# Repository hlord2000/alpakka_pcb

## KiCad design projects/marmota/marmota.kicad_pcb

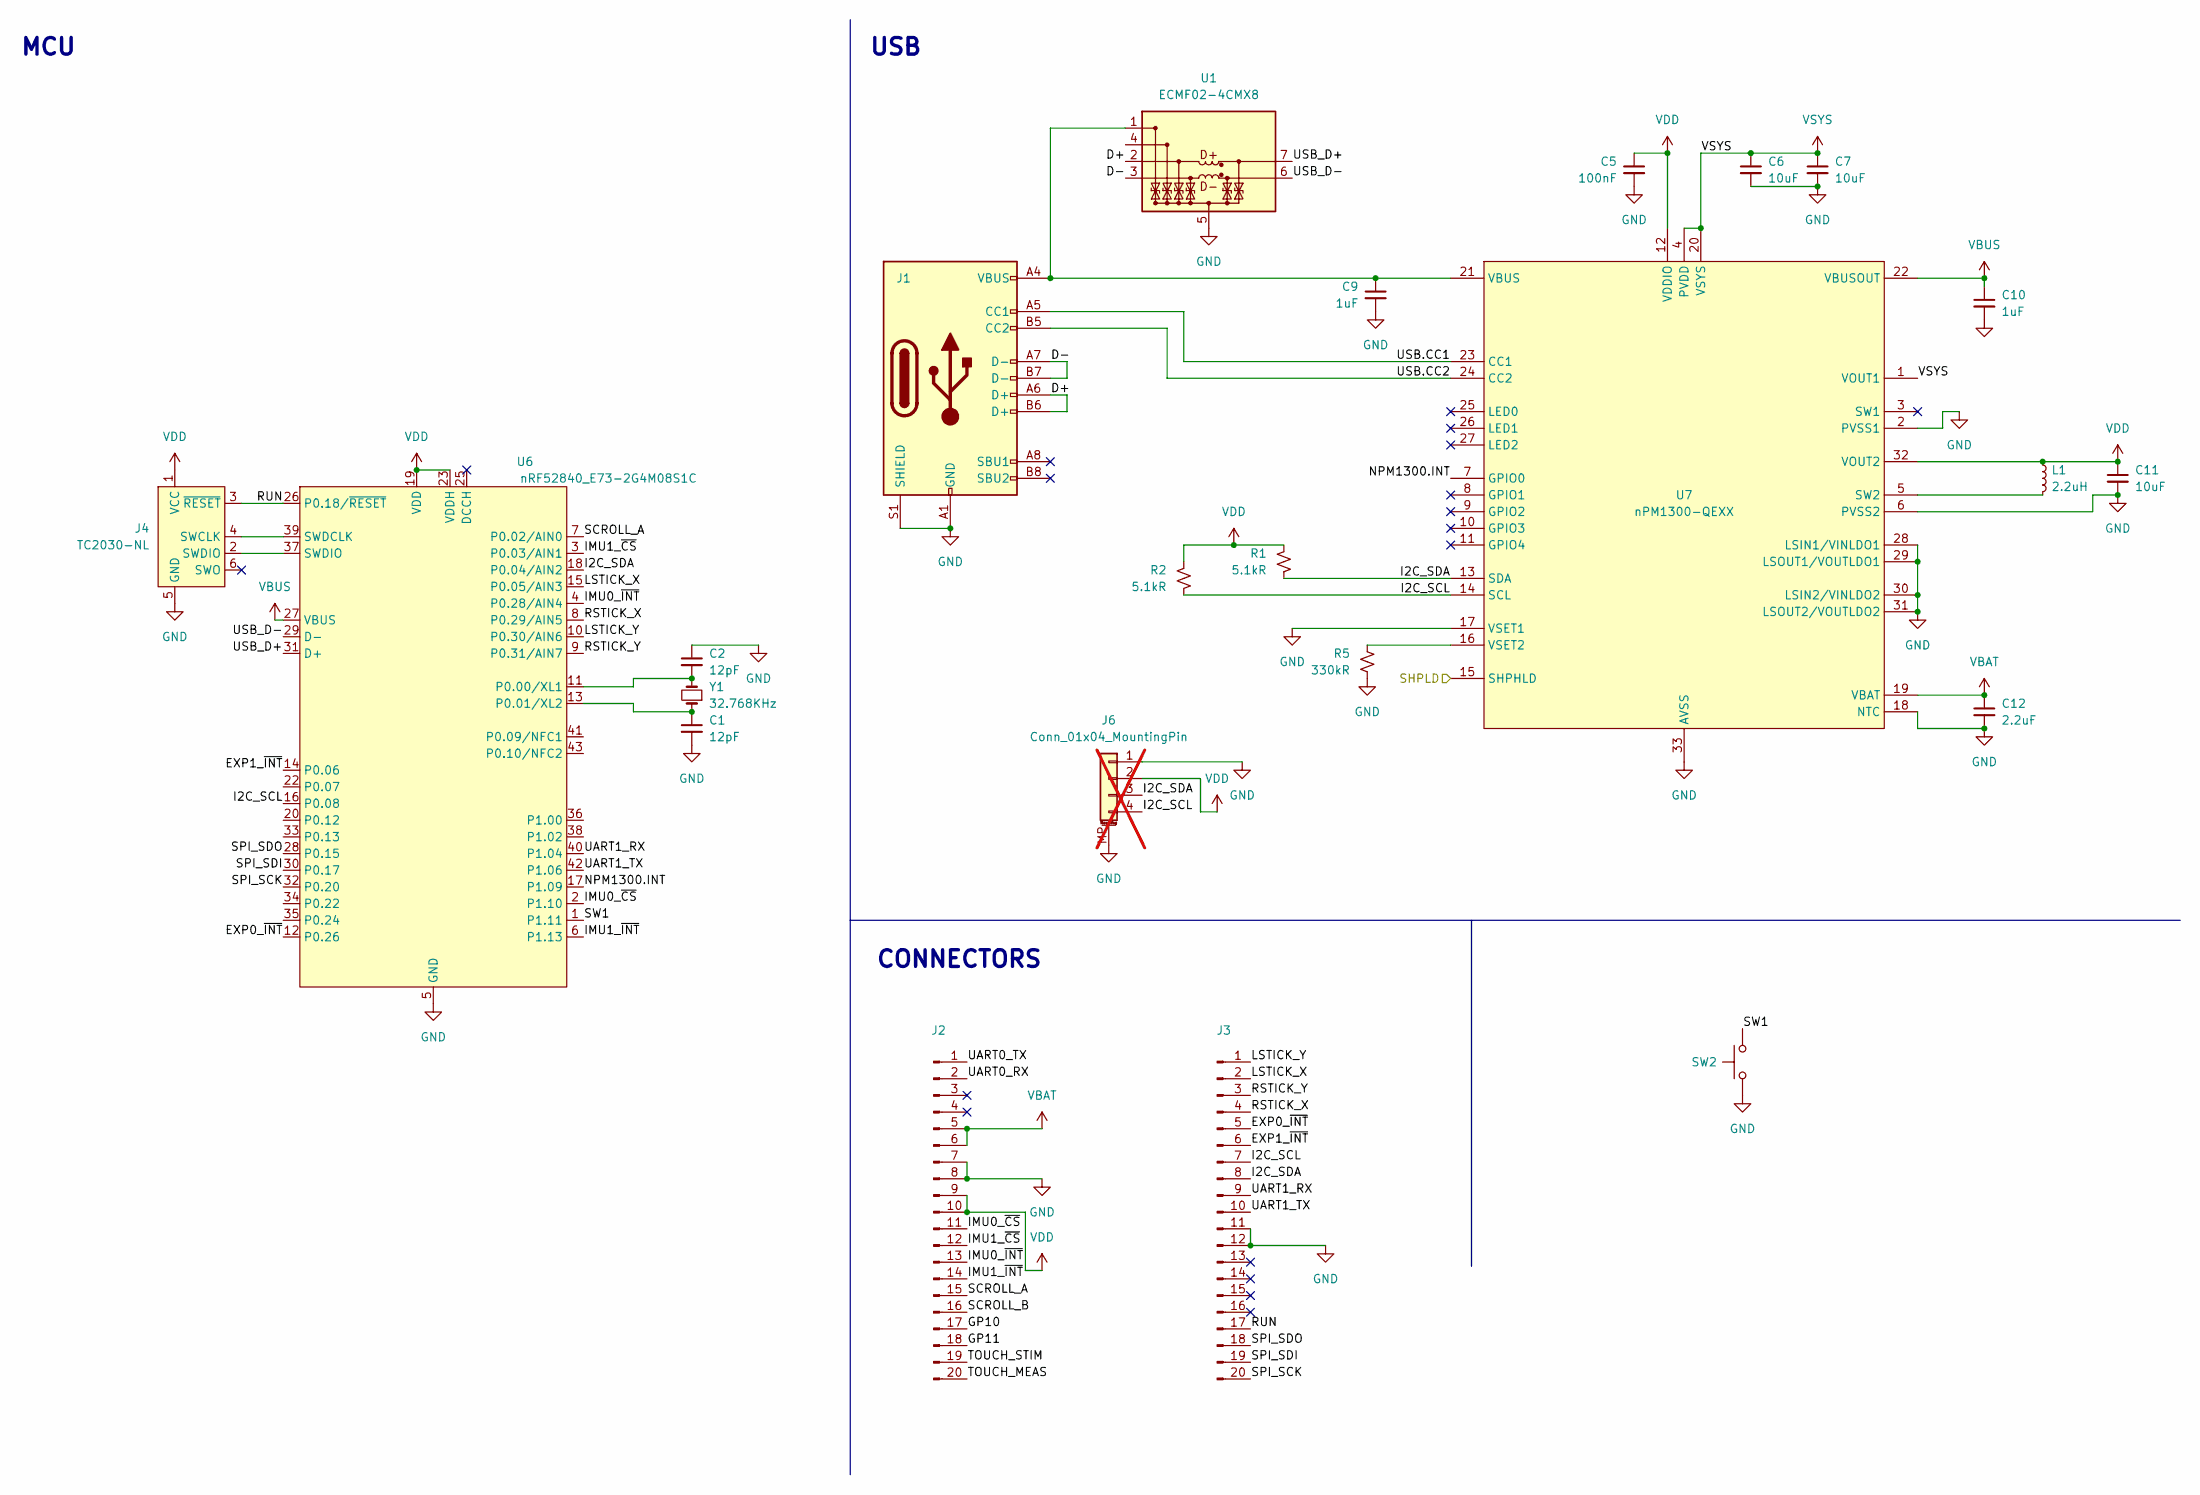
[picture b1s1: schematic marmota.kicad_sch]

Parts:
C1, C2: 12pF; C_0402_1005Metric
C5: 100nF; C_0402_1005Metric; LCSC C307331
C6, C7, C11: 10uF; C_0603_1608Metric; LCSC C96446
C9, C10: 1uF; C_0603_1608Metric; LCSC C15849
C12: 2.2uF; C_0603_1608Metric; LCSC C23630
J1: USB_C; USB_C3019717; LCSC C3019717
J2, J3: Conn_01x20_Pin; Hirose_DF12NB; LCSC C2917815
J4: TC2030-NL; Tag-Connect_TC2030-IDC-NL_2x03_P1.27mm_Vertical
J6: Conn_01x04_MountingPin; JST_SH_SM04B-SRSS-TB_1x04-1MP_P1.00mm_Horizontal; not fitted
L1: 2.2uH; L_0603_1608Metric; LCSC C337910
R1, R2: 5.1kR; R_0402_1005Metric
R5: 330kR; R_0402_1005Metric; LCSC C25778
SW2: Button side; Alpsalpine_SKSC; LCSC C115362
U1: ECMF02-4CMX8; ST_UQFN-8L_1.2x2.5mm_P0.5mm
U6: nRF52840_E73-2G4M08S1C; LCSC C356849
U7: nPM1300-QEXX; QFN-32-1EP_5x5mm_P0.5mm_EP3.6x3.6mm_ThermalVias; LCSC C7466043
Y1: 32.768KHz; Crystal_SMD_2012-2Pin_2.0x1.2mm

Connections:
/D+: J1.A6 (D+), J1.B6 (D+), U1.2 (D-_in)
/D-: J1.A7 (D-), J1.B7 (D-), U1.3 (D+_in)
/EXP0_~INT: J3.5, U6.12 (P0.26)
/EXP1_~INT: J3.6, U6.14 (P0.06)
/GP10: J2.17
/GP11: J2.18
/I2C_SCL: J3.7, J6.4, R2.2, U6.16 (P0.08), U7.14 (SCL)
/I2C_SDA: J3.8, J6.3, R1.2, U6.18 (P0.04/AIN2), U7.13 (SDA)
/IMU0_~CS: J2.11, U6.2 (P1.10)
/IMU0_~INT: J2.13, U6.4 (P0.28/AIN4)
/IMU1_~CS: J2.12, U6.3 (P0.03/AIN1)
/IMU1_~INT: J2.14, U6.6 (P1.13)
/LSTICK_X: J3.2, U6.15 (P0.05/AIN3)
/LSTICK_Y: J3.1, U6.10 (P0.30/AIN6)
/NPM1300.INT: U6.17 (P1.09), U7.7 (GPIO0)
/RSTICK_X: J3.4, U6.8 (P0.29/AIN5)
/RSTICK_Y: J3.3, U6.9 (P0.31/AIN7)
/RUN: J3.17, J4.3 (~RESET), U6.26 (P0.18/~RESET)
/SCROLL_A: J2.15, U6.7 (P0.02/AIN0)
/SCROLL_B: J2.16
/SHPLD: U7.15 (SHPHLD)
/SPI_SCK: J3.20, U6.32 (P0.20)
/SPI_SDI: J3.19, U6.30 (P0.17)
/SPI_SDO: J3.18, U6.28 (P0.15)
/SW1: SW2.2, U6.1 (P1.11)
/TOUCH_MEAS: J2.20
/TOUCH_STIM: J2.19
/UART0_RX: J2.2
/UART0_TX: J2.1
/UART1_RX: J3.9, U6.40 (P1.04)
/UART1_TX: J3.10, U6.42 (P1.06)
/USB.CC1: J1.A5 (CC1), U7.23 (CC1)
/USB.CC2: J1.B5 (CC2), U7.24 (CC2)
/USB_D+: U1.7 (D-_out), U6.31 (D+)
/USB_D-: U1.6 (D+_out), U6.29 (D-)
GND: C1.2, C2.1, C5.2, C6.2, C7.2, C9.2, C10.2, C11.2, C12.2, J1.A1 (GND), J1.A12 (GND), J1.B1 (GND), J1.B12 (GND), J1.S1 (SHIELD), J2.7, J2.8, J3.11, J3.12, J4.5 (GND), J6.1, J6.MP (MountPin), R5.2, SW2.1, U1.5 (GND), U1.8 (GND), U6.5 (GND), U6.21 (GND), U6.24 (GND), U7.2 (PVSS1), U7.6 (PVSS2), U7.17 (VSET1), U7.18 (NTC), U7.28 (LSIN1/VINLDO1), U7.29 (LSOUT1/VOUTLDO1), U7.30 (LSIN2/VINLDO2), U7.31 (LSOUT2/VOUTLDO2), U7.33 (AVSS)
unnamed: J4.4 (SWCLK), U6.39 (SWDCLK)
unnamed: J4.2 (SWDIO), U6.37 (SWDIO)
unnamed: C9.1, J1.A4 (VBUS), J1.A9 (VBUS), J1.B4 (VBUS), J1.B9 (VBUS), U1.1 (VBUS), U7.21 (VBUS)
unnamed: C2.2, U6.11 (P0.00/XL1), Y1.2
unnamed: C1.1, U6.13 (P0.01/XL2), Y1.1
unnamed: L1.2, U7.5 (SW2)
unnamed: R5.1, U7.16 (VSET2)
VBAT: C12.1, J2.5, J2.6, U7.19 (VBAT)
VBUS: C10.1, U6.27 (VBUS), U7.22 (VBUSOUT)
VDD: C5.1, C11.1, J2.9, J2.10, J4.1 (VCC), J6.2, L1.1, R1.1, R2.1, U6.19 (VDD), U6.23 (VDDH), U7.12 (VDDIO), U7.32 (VOUT2)
VSYS: C6.1, C7.1, U7.1 (VOUT1), U7.4 (PVDD), U7.20 (VSYS)

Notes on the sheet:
CONNECTORS
USB
MCU

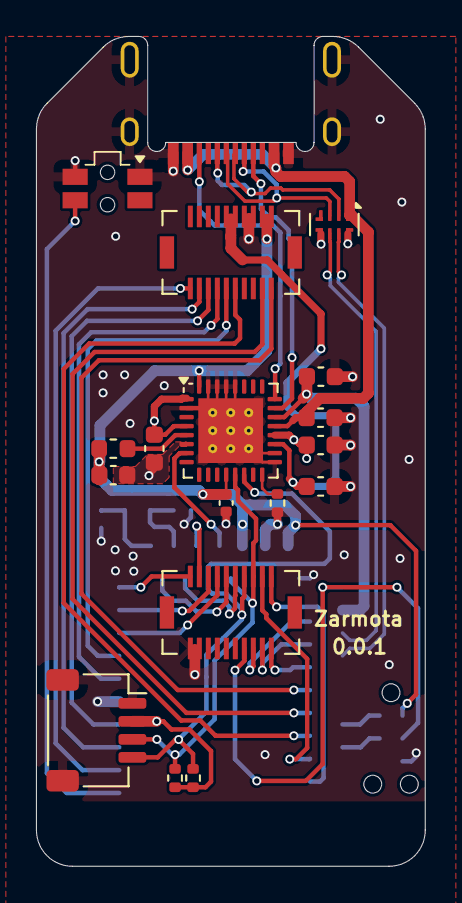
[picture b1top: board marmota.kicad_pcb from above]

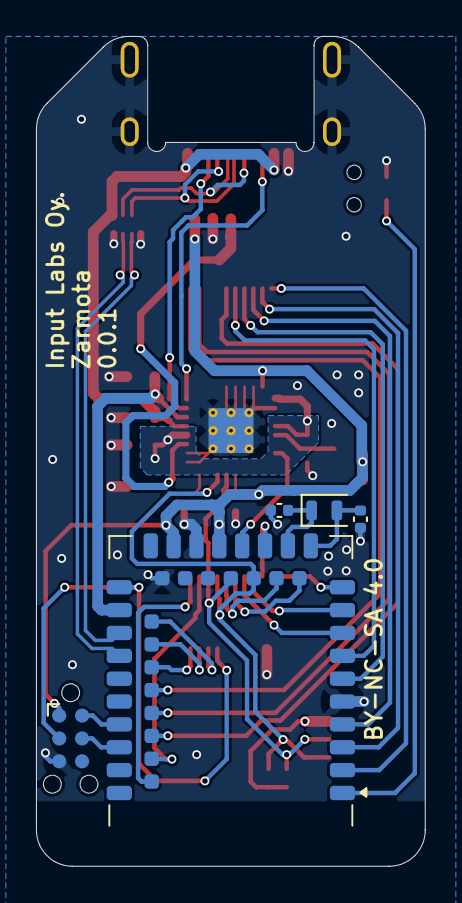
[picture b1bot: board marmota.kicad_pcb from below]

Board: 4 copper layers, 21.6 x 46.1 mm, 23 parts (5 on the bottom side), 39 nets.

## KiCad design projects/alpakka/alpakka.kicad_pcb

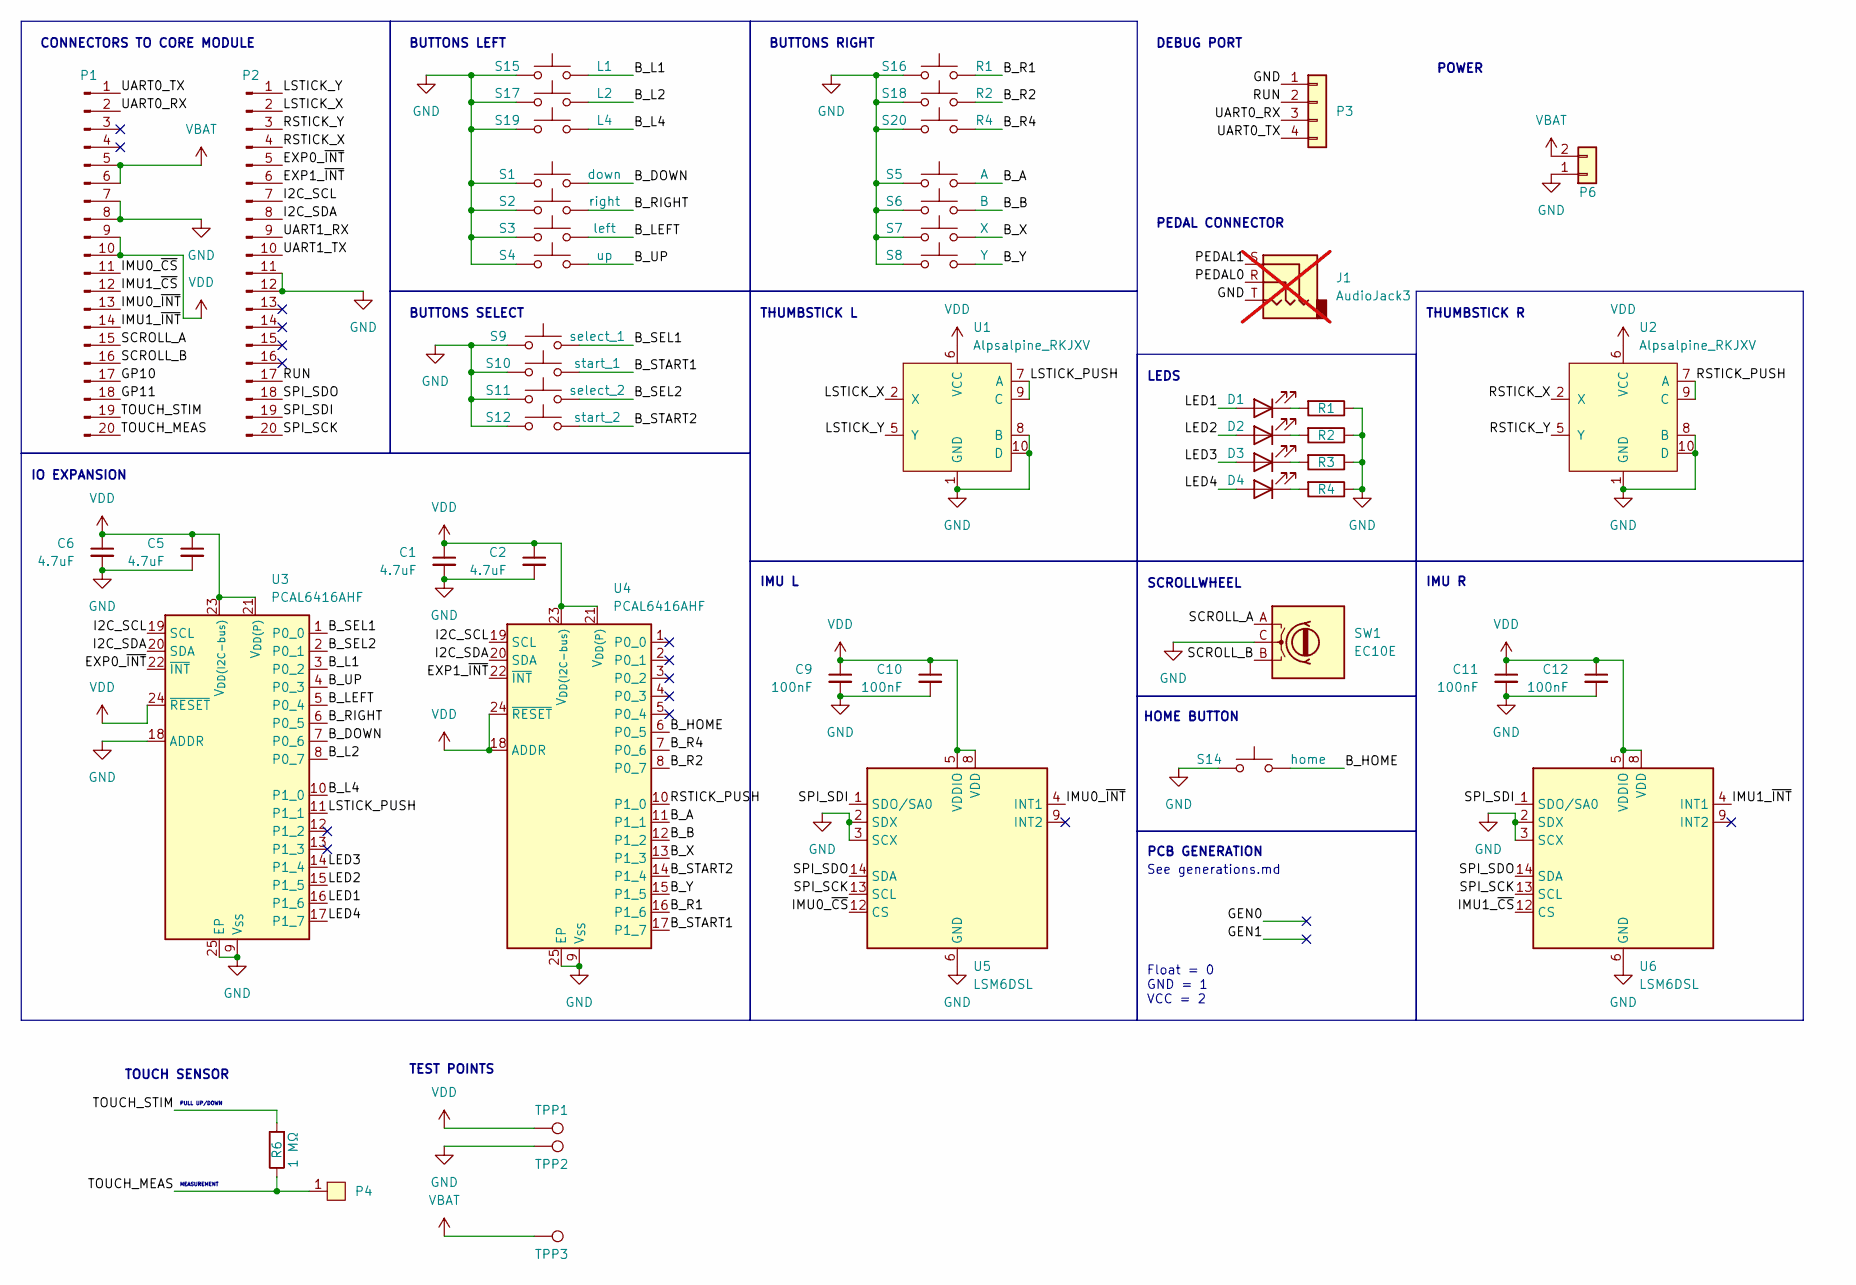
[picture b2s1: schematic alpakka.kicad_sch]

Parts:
C1, C2, C5, C6: 4.7uF; C_0603_1608Metric
C9, C10, C11, C12: 100nF; C_0402_1005Metric
D1, D2, D3, D4: Diode; D_0603_1608Metric; LCSC C2290
J1: AudioJack3; Jack_3.5mm_CUI_SJ-3523-SMT_Horizontal; not fitted
P1, P2: Conn_01x20_Pin; Hirose_DF12NB_receptacle; LCSC C2917814
P3: Conn_01x04; XKB_X6511FRS-04; LCSC C5142237
P4: Blade; HRO_BC-25-3P; LCSC C707322
P6: Conn_01x02; JST_PH_S2B-PH-K_1x02_P2.00mm_Horizontal; LCSC C5359610
R1, R2, R3, R4: 20 Ω; R_0603_1608Metric; LCSC C22950
R6: 1 MΩ; R_0402_1005Metric; LCSC C26083
S1: down; Alpsalpine_SKPM; LCSC C115348
S2: right; Alpsalpine_SKPM; LCSC C115348
S3: left; Alpsalpine_SKPM; LCSC C115348
S4: up; Alpsalpine_SKPM; LCSC C115348
S5: A; Alpsalpine_SKPM; LCSC C115348
S6: B; Alpsalpine_SKPM; LCSC C115348
S7: X; Alpsalpine_SKPM; LCSC C115348
S8: Y; Alpsalpine_SKPM; LCSC C115348
S9: select_1; Alpsalpine_SKPM; LCSC C115348
S10: start_1; Alpsalpine_SKPM; LCSC C115348
S11: select_2; Alpsalpine_SKPM; LCSC C115348
S12: start_2; Alpsalpine_SKPM; LCSC C115348
S14: home; Alpsalpine_SKPM; LCSC C115348
S15: L1; Alpsalpine_SKHHL; LCSC C125031
S16: R1; Alpsalpine_SKHHL; LCSC C125031
S17: L2; Alpsalpine_SKQG; LCSC C202424
S18: R2; Alpsalpine_SKQG; LCSC C202424
S19: L4; Alpsalpine_SKQG; LCSC C202424
S20: R4; Alpsalpine_SKQG; LCSC C202424
SW1: EC10E; Alpsalpine_EC10E
TPP1, TPP2, TPP3: Endpoint; TestPoint_Pad_D1.0mm
U1, U2: Alpsalpine_RKJXV; Alpsalpine_RKJXV122400R
U3, U4: PCAL6416AHF; HVQFN-24-1EP_4x4mm_P0.5mm_EP2.1x2.1mm
U5, U6: LSM6DSL; LGA-14_3x2.5mm_P0.5mm_LayoutBorder3x4y

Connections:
/B_A: S5.2, U4.11 (P1_1)
/B_B: S6.2, U4.12 (P1_2)
/B_DOWN: S1.2, U3.7 (P0_6)
/B_HOME: S14.2, U4.6 (P0_5)
/B_L1: S15.2, U3.3 (P0_2)
/B_L2: S17.2, U3.8 (P0_7)
/B_L4: S19.2, U3.10 (P1_0)
/B_LEFT: S3.2, U3.5 (P0_4)
/B_R1: S16.2, U4.16 (P1_6)
/B_R2: S18.2, U4.8 (P0_7)
/B_R4: S20.2, U4.7 (P0_6)
/B_RIGHT: S2.2, U3.6 (P0_5)
/B_SEL1: S9.2, U3.1 (P0_0)
/B_SEL2: S11.2, U3.2 (P0_1)
/B_START1: S10.2, U4.17 (P1_7)
/B_START2: S12.2, U4.14 (P1_4)
/B_UP: S4.2, U3.4 (P0_3)
/B_X: S7.2, U4.13 (P1_3)
/B_Y: S8.2, U4.15 (P1_5)
/EXP0_~INT: P2.5, U3.22 (~INT)
/EXP1_~INT: P2.6, U4.22 (~INT)
/GP10: P1.17
/GP11: P1.18
/I2C_SCL: P2.7, U3.19 (SCL), U4.19 (SCL)
/I2C_SDA: P2.8, U3.20 (SDA), U4.20 (SDA)
/IMU0_~CS: P1.11, U5.12 (CS)
/IMU0_~INT: P1.13, U5.4 (INT1)
/IMU1_~CS: P1.12, U6.12 (CS)
/IMU1_~INT: P1.14, U6.4 (INT1)
/LED1: D1.2 (A), U3.16 (P1_6)
/LED2: D2.2 (A), U3.15 (P1_5)
/LED3: D3.2 (A), U3.14 (P1_4)
/LED4: D4.2 (A), U3.17 (P1_7)
/LSTICK_PUSH: U1.7 (A), U1.9 (C), U3.11 (P1_1)
/LSTICK_X: P2.2, U1.2 (X)
/LSTICK_Y: P2.1, U1.5 (Y)
/RSTICK_PUSH: U2.7 (A), U2.9 (C), U4.10 (P1_0)
/RSTICK_X: P2.4, U2.2 (X)
/RSTICK_Y: P2.3, U2.5 (Y)
/RUN: P2.17, P3.2
/SCROLL_A: P1.15, SW1.A
/SCROLL_B: P1.16, SW1.B
/SPI_SCK: P2.20, U5.13 (SCL), U6.13 (SCL)
/SPI_SDI: P2.19, U5.1 (SDO/SA0), U6.1 (SDO/SA0)
/SPI_SDO: P2.18, U5.14 (SDA), U6.14 (SDA)
/TOUCH_MEAS: P1.20, P4.1, R6.1
/TOUCH_STIM: P1.19, R6.2
/UART0_RX: P1.2, P3.3
/UART0_TX: P1.1, P3.4
/UART1_RX: P2.9
/UART1_TX: P2.10
GND: C1.2, C2.2, C5.2, C6.2, C9.2, C10.2, C11.2, C12.2, J1.T, P1.7, P1.8, P2.11, P2.12, P3.1, P6.1, R1.1, R2.1, R3.1, R4.1, S1.1, S2.1, S3.1, S4.1, S5.1, S6.1, S7.1, S8.1, S9.1, S10.1, S11.1, S12.1, S14.1, S15.1, S16.1, S17.1, S18.1, S19.1, S20.1, SW1.C, TPP2.1, U1.1 (GND), U1.4 (GND), U1.8 (B), U1.10 (D), U2.1 (GND), U2.4 (GND), U2.8 (B), U2.10 (D), U3.9 (V_{SS}), U3.18 (ADDR), U3.25 (EP), U4.9 (V_{SS}), U4.25 (EP), U5.2 (SDX), U5.3 (SCX), U5.6 (GND), U5.7 (GND), U6.2 (SDX), U6.3 (SCX), U6.6 (GND), U6.7 (GND)
unnamed: D1.1 (K), R1.2
unnamed: D2.1 (K), R2.2
unnamed: D3.1 (K), R3.2
unnamed: D4.1 (K), R4.2
VBAT: P1.5, P1.6, P6.2, TPP3.1
VDD: C1.1, C2.1, C5.1, C6.1, C9.1, C10.1, C11.1, C12.1, P1.9, P1.10, TPP1.1, U1.3 (VCC), U1.6 (VCC), U2.3 (VCC), U2.6 (VCC), U3.21 (V_{DD(P)}), U3.23 (V_{DD(I2C-bus)}), U3.24 (~RESET), U4.18 (ADDR), U4.21 (V_{DD(P)}), U4.23 (V_{DD(I2C-bus)}), U4.24 (~RESET), U5.5 (VDDIO), U5.8 (VDD), U6.5 (VDDIO), U6.8 (VDD)

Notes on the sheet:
SCROLLWHEEL
DEBUG PORT
THUMBSTICK R
THUMBSTICK L
IMU L
PCB GENERATION
HOME BUTTON
BUTTONS SELECT
Float = 0 GND = 1 VCC = 2
TEST POINTS
CONNECTORS TO CORE MODULE
PEDAL CONNECTOR
TOUCH SENSOR
IO EXPANSION
LEDS
BUTTONS LEFT
MEASUREMENT
BUTTONS RIGHT
IMU R
POWER
See generations.md
PULL UP/DOWN

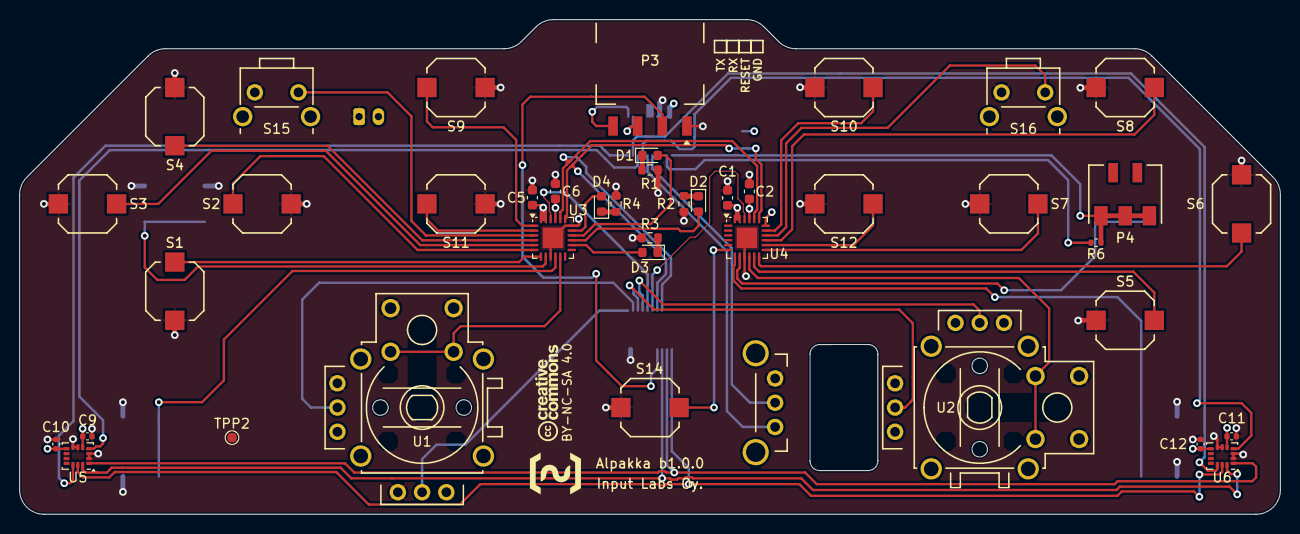
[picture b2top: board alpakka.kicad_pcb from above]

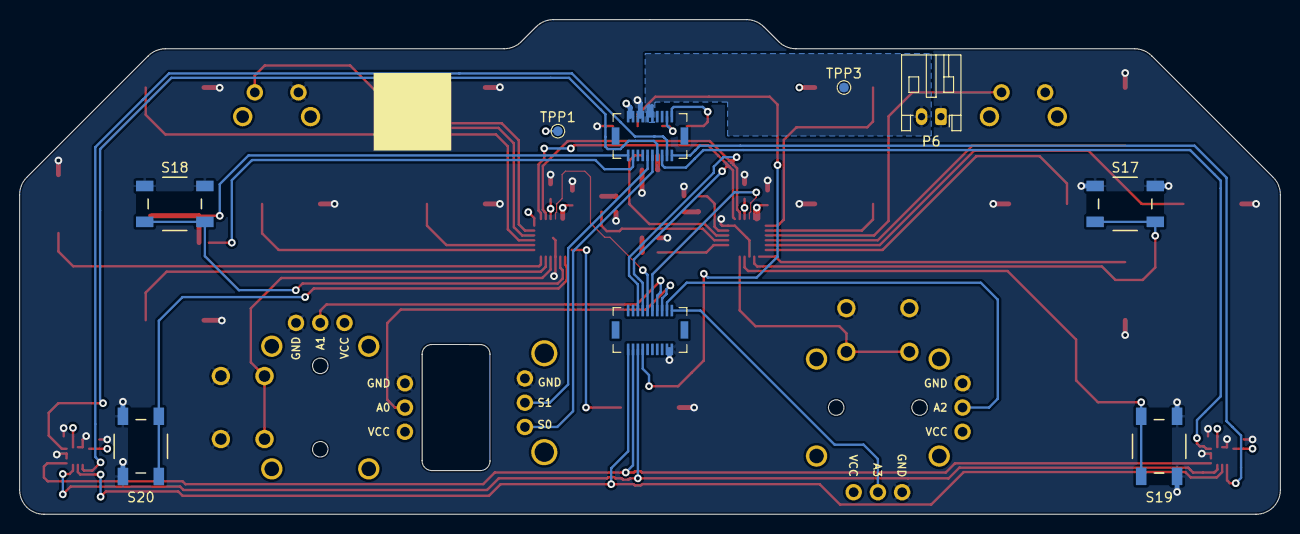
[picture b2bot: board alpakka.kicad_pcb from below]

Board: 4 copper layers, 130.0 x 51.0 mm, 51 parts (9 on the bottom side), 54 nets.

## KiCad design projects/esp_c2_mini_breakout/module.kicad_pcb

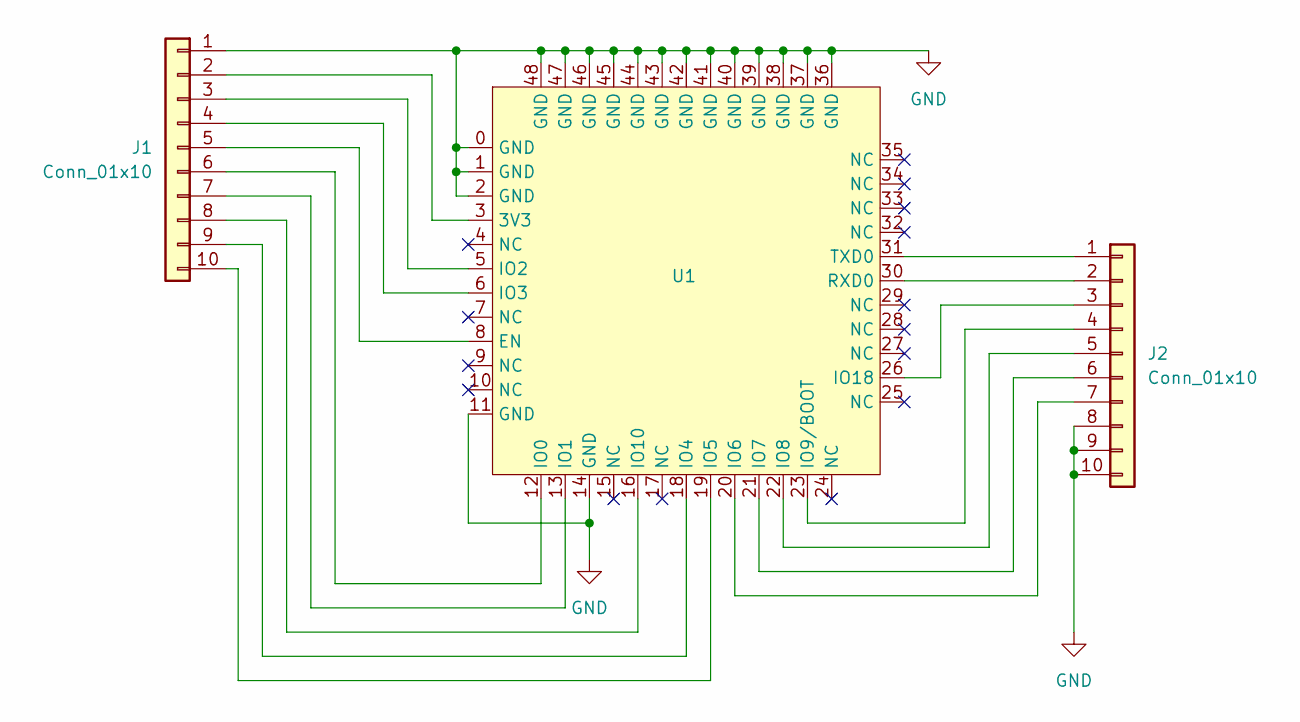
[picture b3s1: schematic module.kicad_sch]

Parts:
J1, J2: Conn_01x10; PinHeader_1x10_P2.54mm_Vertical
U1: Espressif_ESP32_mini; LCSC C3013915

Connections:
GND: J1.1, J2.8, J2.9, J2.10, U1.0 (GND), U1.1 (GND), U1.2 (GND), U1.11 (GND), U1.14 (GND), U1.36 (GND), U1.37 (GND), U1.38 (GND), U1.39 (GND), U1.40 (GND), U1.41 (GND), U1.42 (GND), U1.43 (GND), U1.44 (GND), U1.45 (GND), U1.46 (GND), U1.47 (GND), U1.48 (GND)
unnamed: J1.2, U1.3 (3V3)
unnamed: J1.3, U1.5 (IO2)
unnamed: J1.4, U1.6 (IO3)
unnamed: J1.5, U1.8 (EN)
unnamed: J1.6, U1.12 (IO0)
unnamed: J1.7, U1.13 (IO1)
unnamed: J1.8, U1.16 (IO10)
unnamed: J1.9, U1.18 (IO4)
unnamed: J1.10, U1.19 (IO5)
unnamed: J2.1, U1.31 (TXD0)
unnamed: J2.2, U1.30 (RXD0)
unnamed: J2.3, U1.26 (IO18)
unnamed: J2.4, U1.23 (IO9/BOOT)
unnamed: J2.5, U1.22 (IO8)
unnamed: J2.6, U1.21 (IO7)
unnamed: J2.7, U1.20 (IO6)

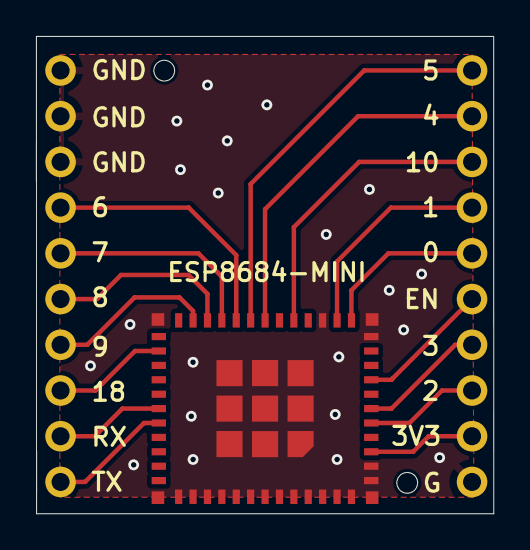
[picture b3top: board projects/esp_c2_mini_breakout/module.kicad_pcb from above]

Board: 2 copper layers, 25.4 x 26.5 mm, 3 parts (0 on the bottom side), 17 nets.

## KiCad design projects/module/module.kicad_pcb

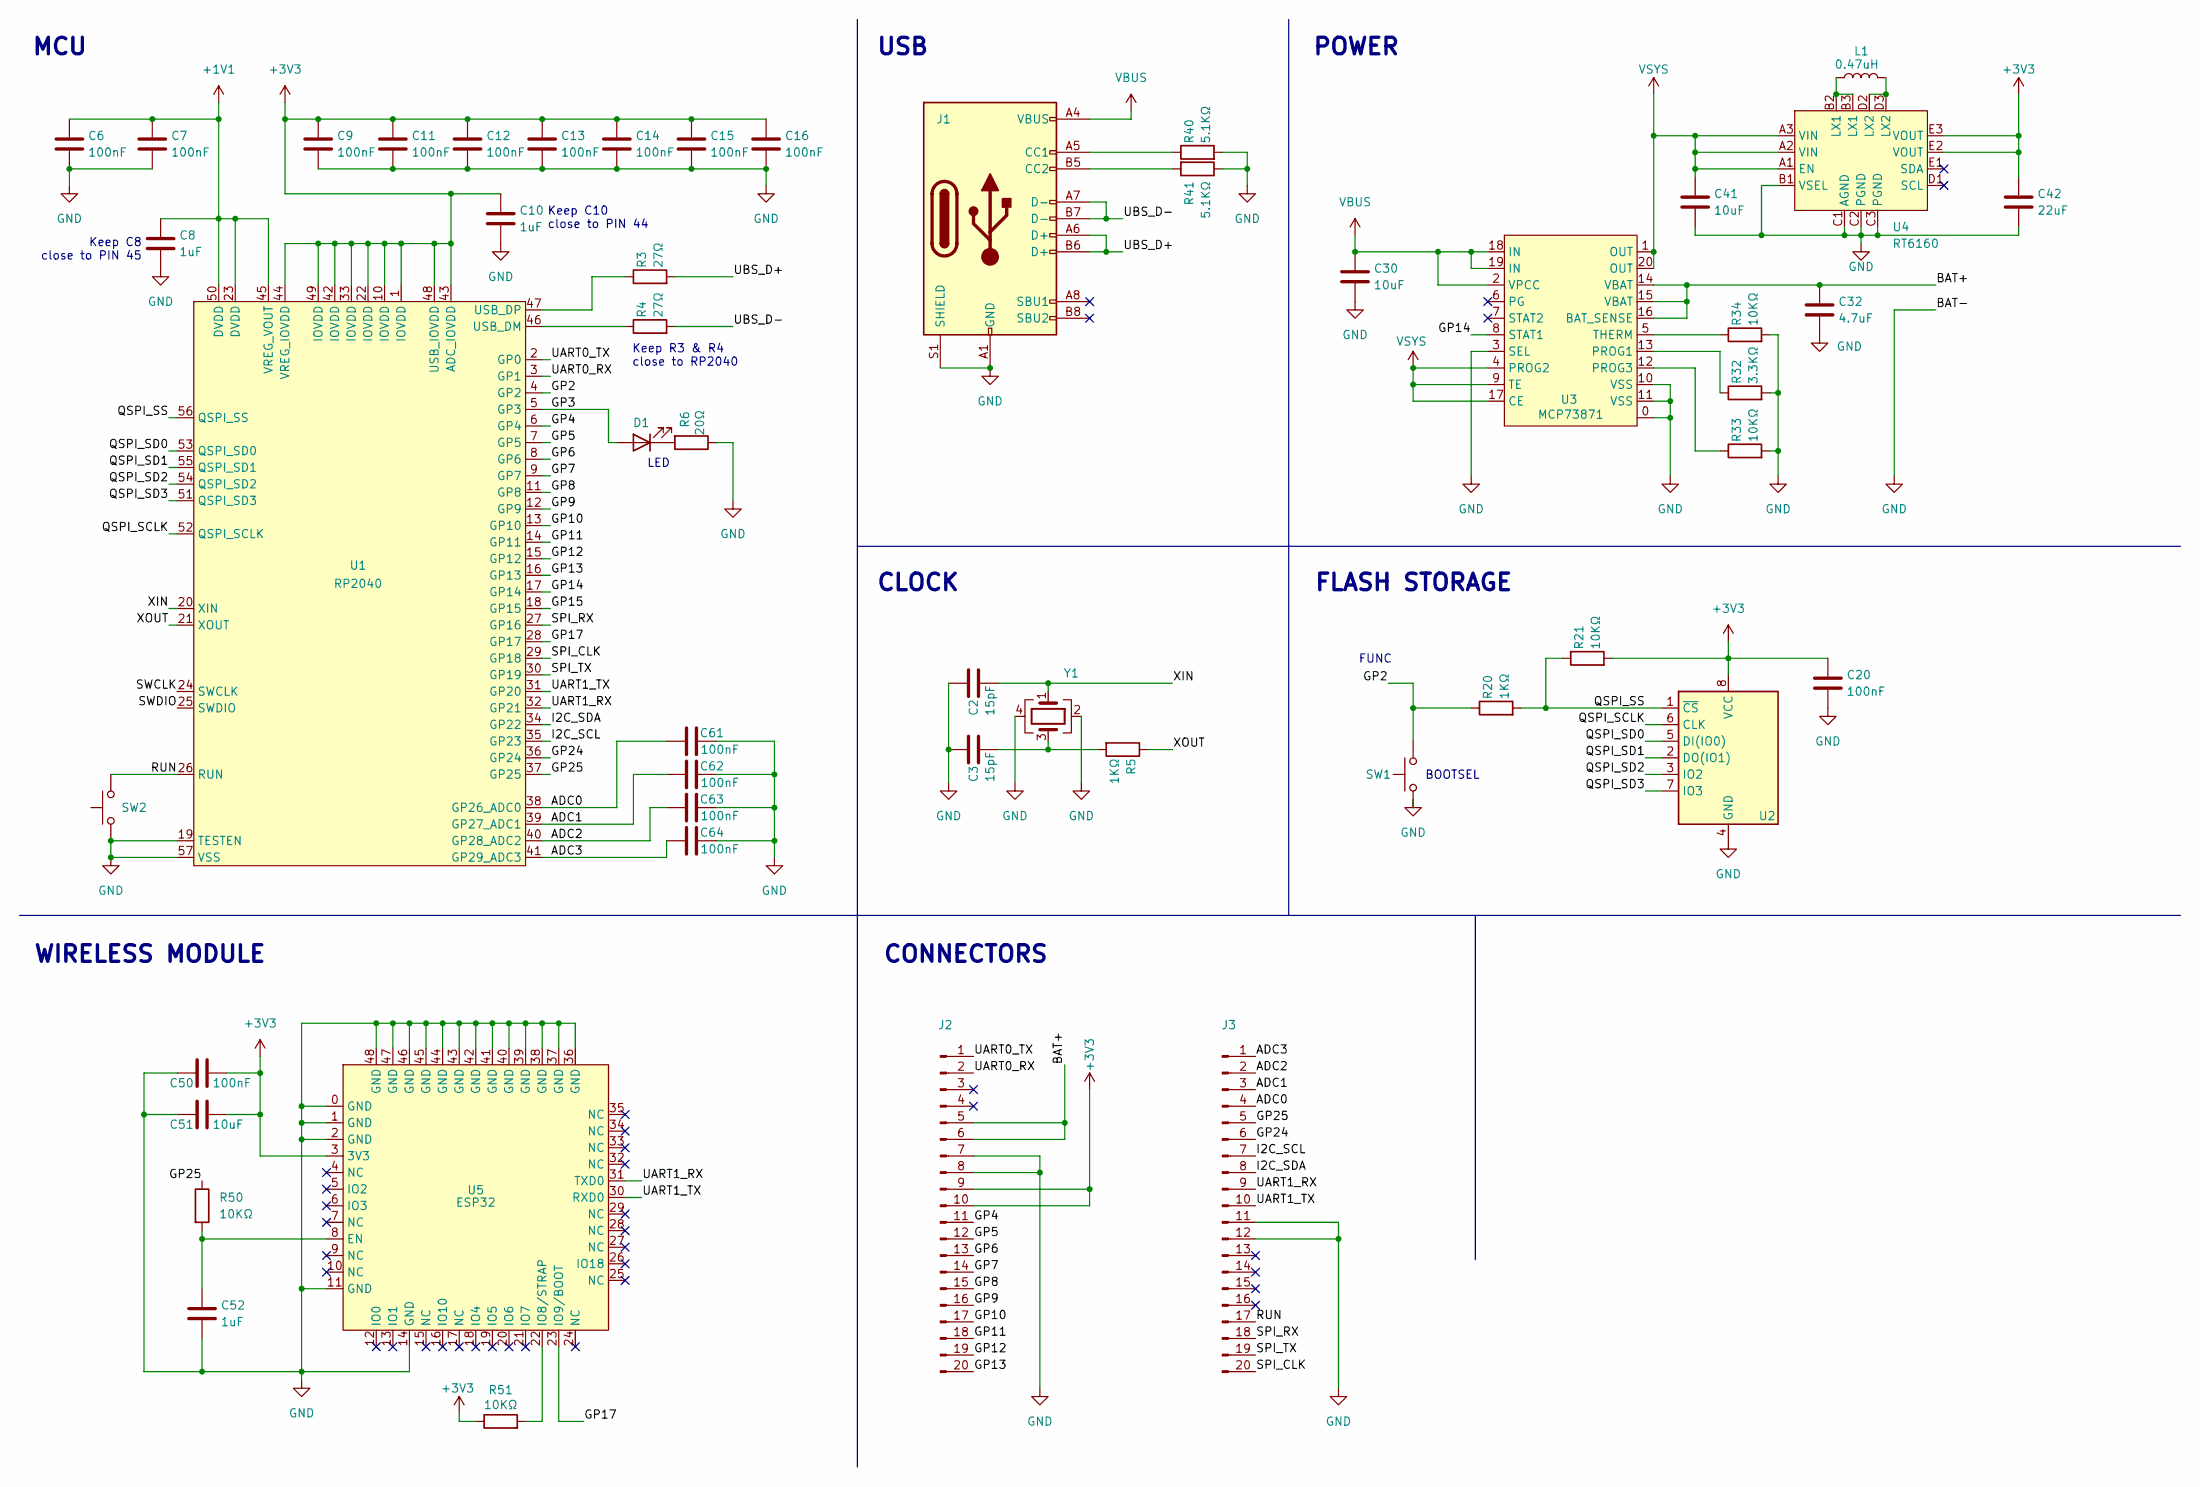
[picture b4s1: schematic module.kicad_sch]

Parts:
C2, C3: 15pF; 0402_compact; LCSC C1548
C6, C7, C9, C11, C12, C13, C14, C15, C16, C20, C50, C61, C62, C63, C64: 100nF; 0402_compact; LCSC C1525
C8, C10, C52: 1uF; 0402_compact; LCSC C52923
C30, C41, C51: 10uF; 0402_compact; LCSC C15525
C32: 4.7uF; 0402_compact; LCSC C23733
C42: 22uF; 0402_compact; LCSC C105226
D1: Diode; 0603_d; LCSC C2290
J1: USB_C; USB_C3019717; LCSC C3019717
J2, J3: Conn_01x20_Pin; Hirose_DF12NB; LCSC C2917815
L1: 0.47uH; 0603_compact; LCSC C341701
R3, R4: 27Ω; 0402_compact; LCSC C25100
R5, R20: 1KΩ; 0402_compact; LCSC C11702
R6: 20Ω; 0603; LCSC C22950
R21, R33, R34, R50, R51: 10KΩ; 0402_compact; LCSC C25744
R32: 3.3KΩ; 0402_compact; LCSC C137992
R40, R41: 5.1KΩ; 0402_compact; LCSC C25905
SW1: Button top; Alpsalpine_SKRP_compact; LCSC C139797
SW2: Button side; Alpsalpine_SKSC; LCSC C115362
U1: RP2040; QFN-56-1EP_7x7mm_P0.4mm_EP3.2x3.2mm; LCSC C2040
U2: FLASH; Winbond_W25Q; LCSC C2843335
U3: MCP73871; QFN20_internal_routing; LCSC C511310
U4: RT6160; WL-CSP-15B-1.4x2.3; LCSC C7065276
U5: ESP32; Espressif_ESP32_mini; LCSC C3013915
Y1: 12MHz; Crystal_SMD_2520-4Pin_2.5x2.0mm; LCSC C2149205

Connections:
+1V1: C6.2, C7.2, C8.2, U1.23 (DVDD), U1.45 (VREG_VOUT), U1.50 (DVDD)
+3V3: C9.2, C10.2, C11.2, C12.2, C13.2, C14.2, C15.2, C16.2, C20.2, C42.2, C50.2, C51.2, J2.9, J2.10, R21.2, R51.1, U1.1 (IOVDD), U1.10 (IOVDD), U1.22 (IOVDD), U1.33 (IOVDD), U1.42 (IOVDD), U1.43 (ADC_IOVDD), U1.44 (VREG_IOVDD), U1.48 (USB_IOVDD), U1.49 (IOVDD), U2.8 (VCC), U4.E2 (VOUT), U4.E3 (VOUT), U5.3 (3V3)
/ADC0: C61.2, J3.4, U1.38 (GP26_ADC0)
/ADC1: C62.2, J3.3, U1.39 (GP27_ADC1)
/ADC2: C63.2, J3.2, U1.40 (GP28_ADC2)
/ADC3: C64.2, J3.1, U1.41 (GP29_ADC3)
/BAT+: C32.2, J2.5, J2.6, U3.14 (VBAT), U3.15 (VBAT), U3.16 (BAT_SENSE)
/GP2: R20.1, SW1.2, U1.4 (GP2)
/GP3: D1.2 (A), U1.5 (GP3)
/GP4: J2.11, U1.6 (GP4)
/GP5: J2.12, U1.7 (GP5)
/GP6: J2.13, U1.8 (GP6)
/GP7: J2.14, U1.9 (GP7)
/GP8: J2.15, U1.11 (GP8)
/GP9: J2.16, U1.12 (GP9)
/GP10: J2.17, U1.13 (GP10)
/GP11: J2.18, U1.14 (GP11)
/GP12: J2.19, U1.15 (GP12)
/GP13: J2.20, U1.16 (GP13)
/GP14: U1.17 (GP14), U3.8 (STAT1)
/GP15: U1.18 (GP15)
/GP17: U1.28 (GP17), U5.23 (IO9/BOOT)
/GP24: J3.6, U1.36 (GP24)
/GP25: J3.5, R50.1, U1.37 (GP25)
/I2C_SCL: J3.7, U1.35 (GP23)
/I2C_SDA: J3.8, U1.34 (GP22)
/QSPI_SCLK: U1.52 (QSPI_SCLK), U2.6 (CLK)
/QSPI_SD0: U1.53 (QSPI_SD0), U2.5 (DI(IO0))
/QSPI_SD1: U1.55 (QSPI_SD1), U2.2 (DO(IO1))
/QSPI_SD2: U1.54 (QSPI_SD2), U2.3 (IO2)
/QSPI_SD3: U1.51 (QSPI_SD3), U2.7 (IO3)
/QSPI_SS: R20.2, R21.1, U1.56 (QSPI_SS), U2.1 (~CS)
/RUN: J3.17, SW2.2, U1.26 (RUN)
/SPI_CLK: J3.20, U1.29 (GP18)
/SPI_RX: J3.18, U1.27 (GP16)
/SPI_TX: J3.19, U1.30 (GP19)
/SWCLK: U1.24 (SWCLK)
/SWDIO: U1.25 (SWDIO)
/UART0_RX: J2.2, U1.3 (GP1)
/UART0_TX: J2.1, U1.2 (GP0)
/UART1_RX: J3.9, U1.32 (GP21), U5.31 (TXD0)
/UART1_TX: J3.10, U1.31 (GP20), U5.30 (RXD0)
/UBS_D+: J1.A6 (D+), J1.B6 (D+), R3.2
/UBS_D-: J1.A7 (D-), J1.B7 (D-), R4.2
/XIN: C2.1, U1.20 (XIN), Y1.1
/XOUT: R5.1, U1.21 (XOUT)
GND: C2.2, C3.2, C6.1, C7.1, C8.1, C9.1, C10.1, C11.1, C12.1, C13.1, C14.1, C15.1, C16.1, C20.1, C30.1, C32.1, C41.1, C42.1, C50.1, C51.1, C52.1, C61.1, C62.1, C63.1, C64.1, J1.A1 (GND), J1.A12 (GND), J1.B1 (GND), J1.B12 (GND), J1.S1 (SHIELD), J2.7, J2.8, J3.11, J3.12, R6.1, R32.2, R33.2, R34.2, R40.2, R41.1, SW1.1, SW2.1, U1.19 (TESTEN), U1.57 (VSS), U2.4 (GND), U3.0, U3.3 (SEL), U3.10 (VSS), U3.11 (VSS), U4.B1 (VSEL), U4.C1 (AGND), U4.C2 (PGND), U4.C3 (PGND), U5.0 (GND), U5.1 (GND), U5.2 (GND), U5.11 (GND), U5.14 (GND), U5.36 (GND), U5.37 (GND), U5.38 (GND), U5.39 (GND), U5.40 (GND), U5.41 (GND), U5.42 (GND), U5.43 (GND), U5.44 (GND), U5.45 (GND), U5.46 (GND), U5.47 (GND), U5.48 (GND), Y1.2, Y1.4
unnamed: C3.1, R5.2, Y1.3
unnamed: D1.1 (K), R6.2
unnamed: J1.A5 (CC1), R40.1
unnamed: J1.B5 (CC2), R41.2
unnamed: L1.1, U4.B2 (LX1), U4.B3 (LX1)
unnamed: L1.2, U4.D2 (LX2), U4.D3 (LX2)
unnamed: R4.1, U1.46 (USB_DM)
unnamed: R3.1, U1.47 (USB_DP)
unnamed: R32.1, U3.13 (PROG1)
unnamed: R33.1, U3.12 (PROG3)
unnamed: R34.1, U3.5 (THERM)
unnamed: C52.2, R50.2, U5.8 (EN)
unnamed: R51.2, U5.22 (IO8/STRAP)
VBUS: C30.2, J1.A4 (VBUS), J1.A9 (VBUS), J1.B4 (VBUS), J1.B9 (VBUS), U3.2 (VPCC), U3.18 (IN), U3.19 (IN)
VSYS: C41.2, U3.1 (OUT), U3.4 (PROG2), U3.9 (TE), U3.17 (CE), U3.20 (OUT), U4.A1 (EN), U4.A2 (VIN), U4.A3 (VIN)

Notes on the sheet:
POWER
CONNECTORS
USB
Keep R3 & R4 close to RP2040
WIRELESS MODULE
Keep C8 close to PIN 45
CLOCK
FUNC
LED
BOOTSEL
FLASH STORAGE
Keep C10 close to PIN 44
MCU

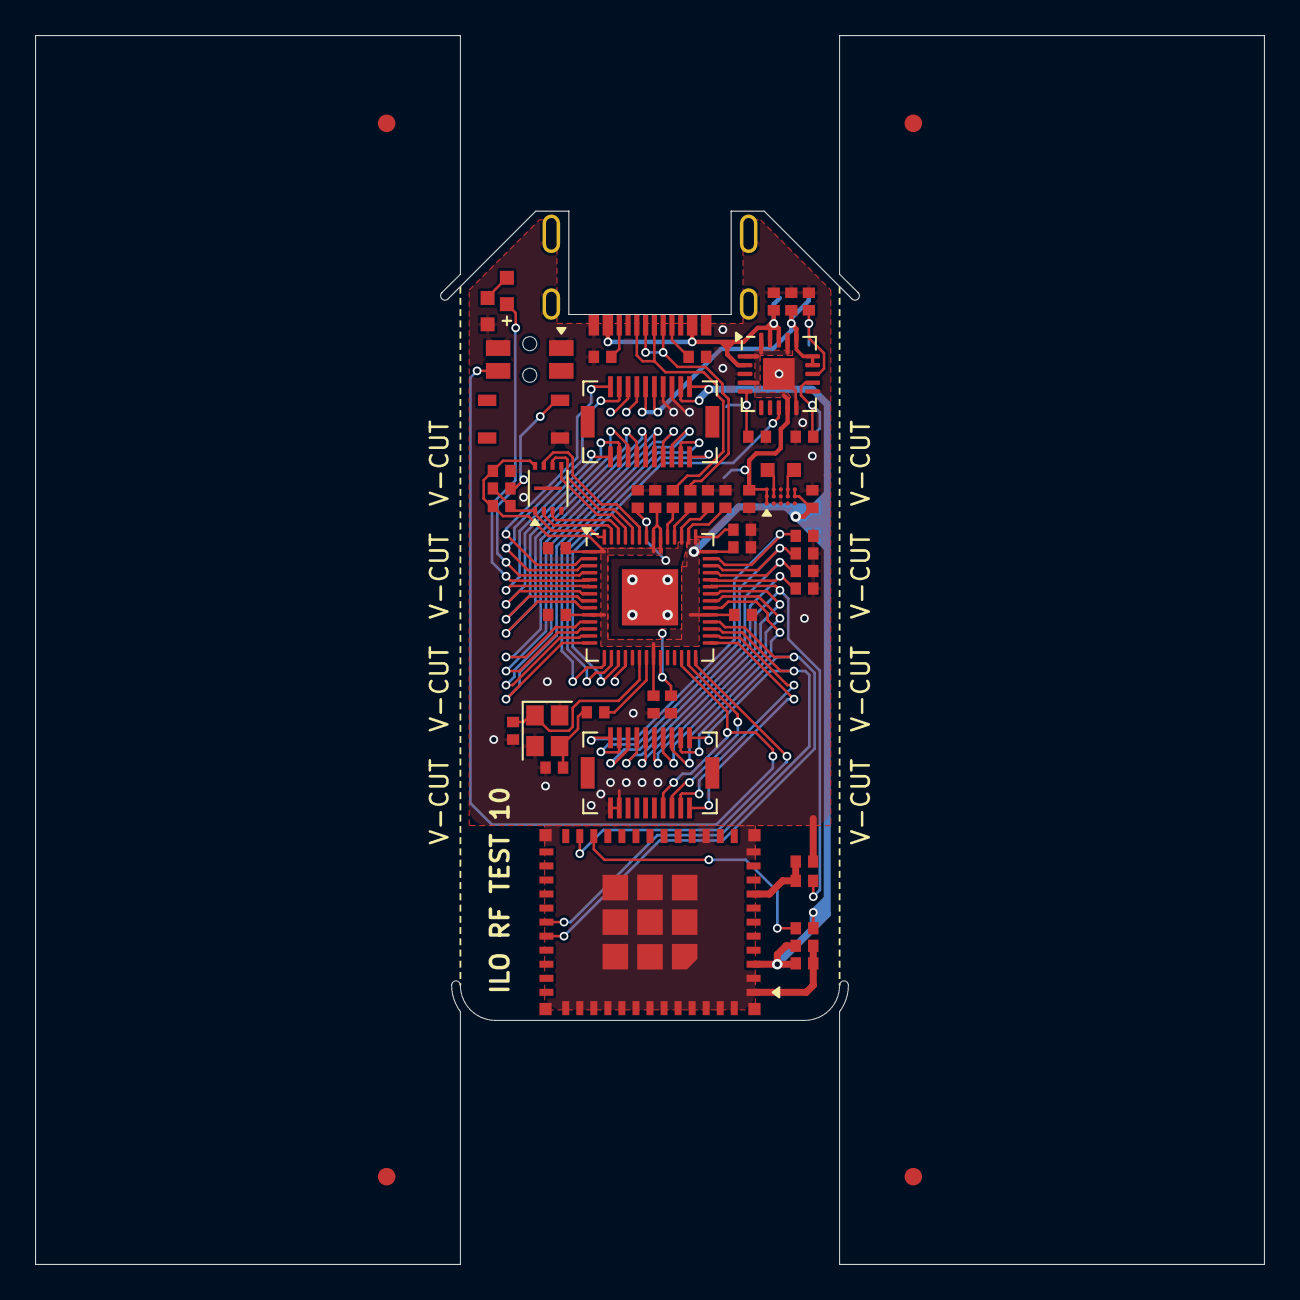
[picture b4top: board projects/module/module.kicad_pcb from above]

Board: 2 copper layers, 70.0 x 70.0 mm, 51 parts (0 on the bottom side), 59 nets.
